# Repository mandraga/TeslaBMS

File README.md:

## Adaptation to Teensy 4.

This fork branches to adapt to the Teensy 4, it needs an interface board pcb or a carrier board redesign.
See the VW BMS fork or the pull request at the original repo for adapter PCB in Kicad format.

# TeslaBMS

Based off work done by Collin Kidder

Designed to work with my own board design and a Teensy 3.2

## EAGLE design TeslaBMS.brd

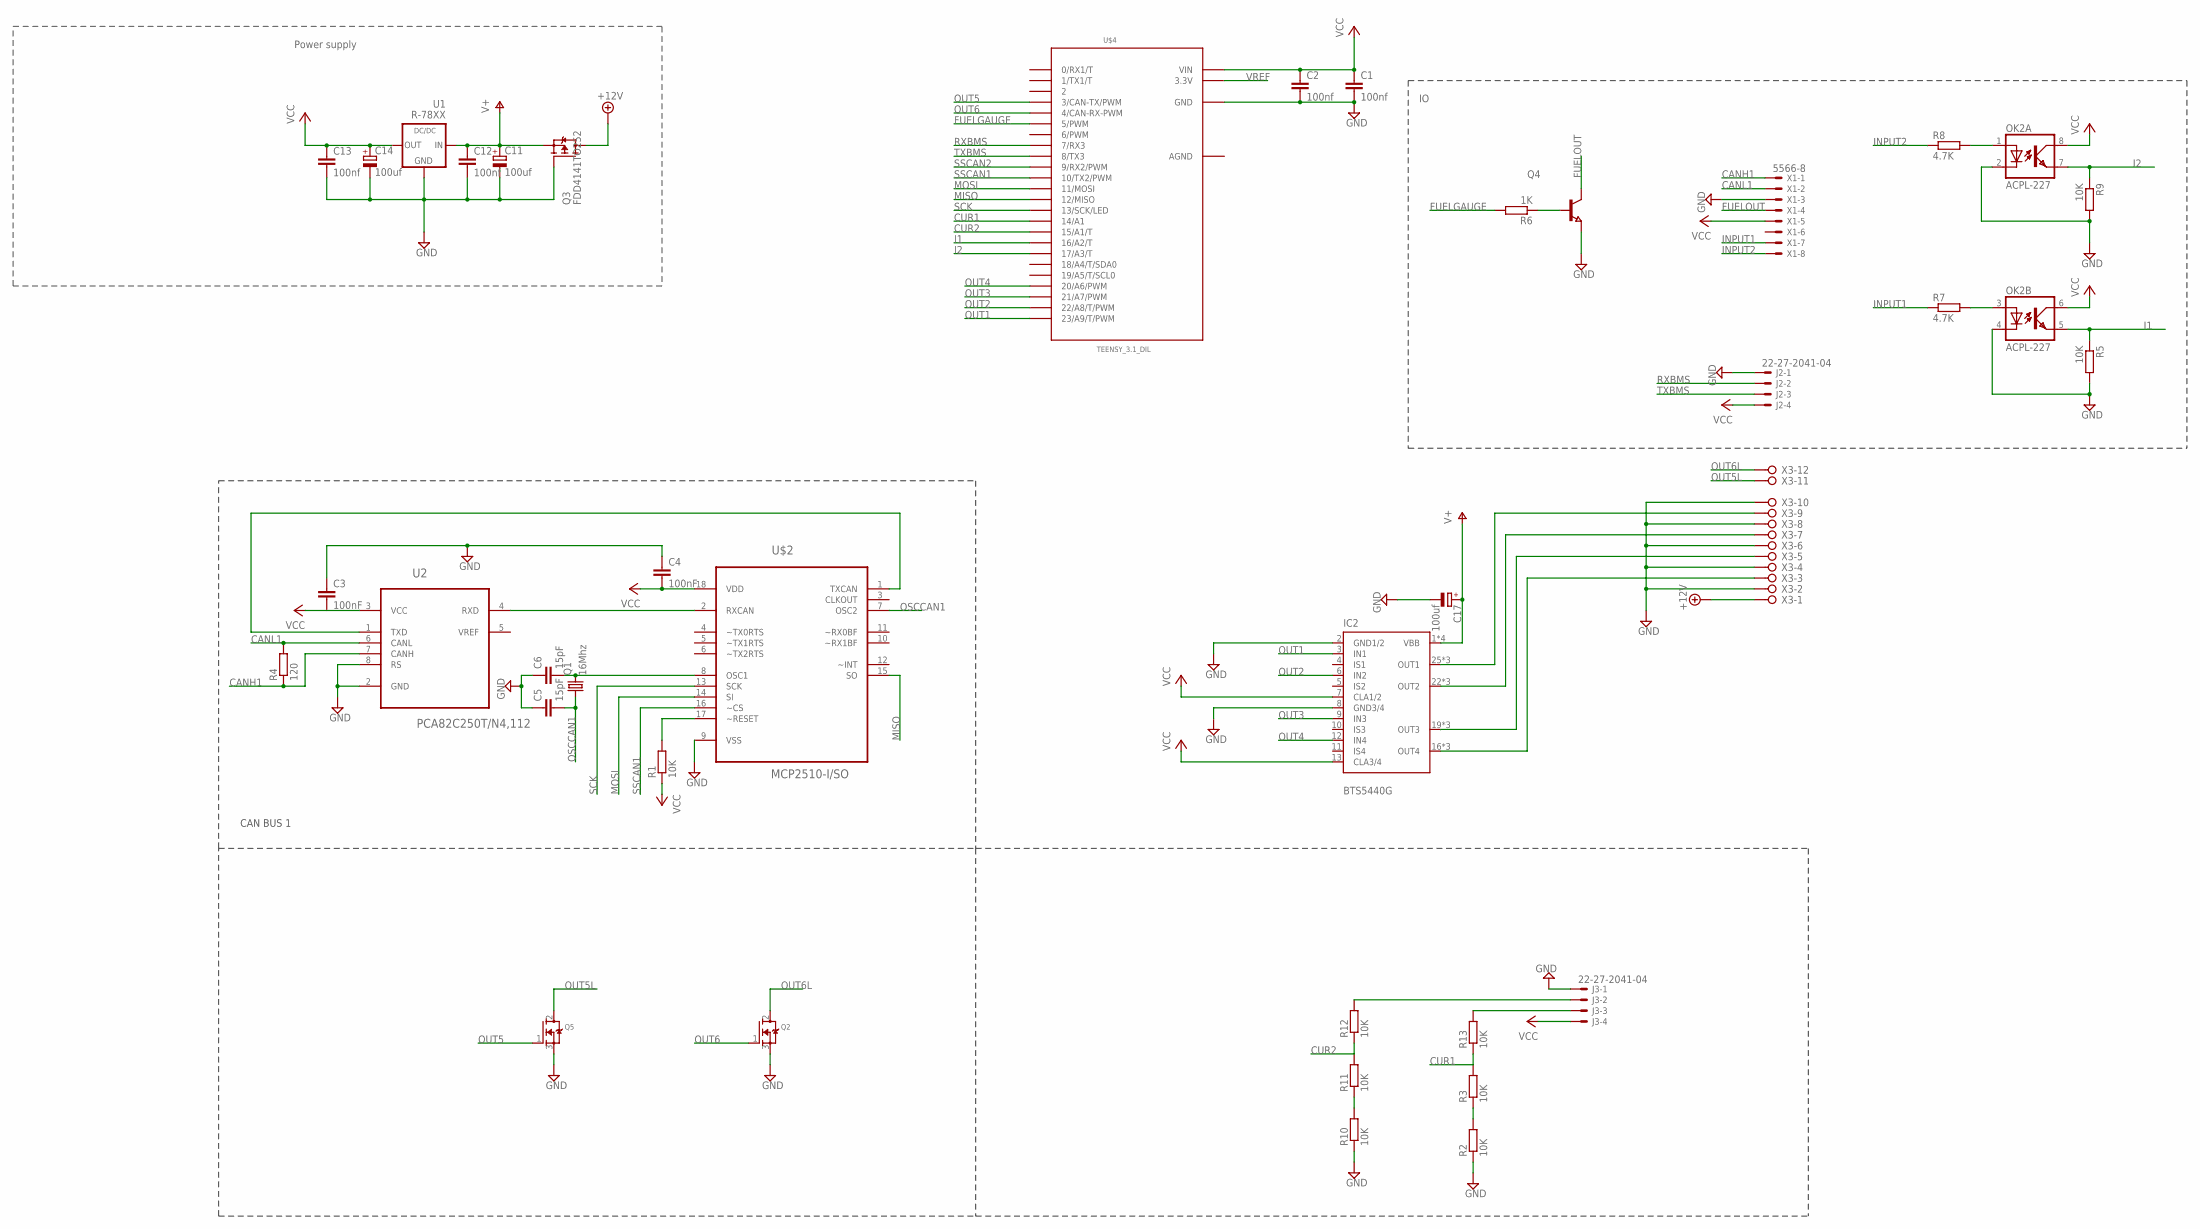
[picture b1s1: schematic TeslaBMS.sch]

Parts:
C1, C2, C12, C13: 100nf; C0805
C3, C4: 100nF; C0805
C5, C6: 15pF; C0805
C11, C14, C17: 100uf; 153CLV-0810
IC2: BTS5440G; PG-DSO-28
J2, J3: 22-27-2041-04; 6410-04
OK2: ACPL-227; SOIC08
Q1: 16Mhz; SM49
Q2, Q5: MOSFET-NGDS_TO220V; TO220V
Q3: FDD4141TO252; TO252
Q4: NPN-TRANSISTOR_SOT23; SOT23
R1, R2, R3, R5, R9, R10, R11, R12, R13: 10K; R0805
R4: 120; R0805
R6: 1K; R0805
R7, R8: 4.7K; R0805
U1: R-78XX
U2: PCA82C250T/N4,112; SOIC127P600X175-8N
U$2: MCP2510-I/SO; SOIC127P1034X264-18N
U$4: TEENSY_3.1_DIL; TEENSY3-DIL
X1: 5566-8
X3: W237-12P

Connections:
+12V: Q3.3 (D), X3.1
AGND: U$4.AGND
CANH1: R4.1, U2.7 (CANH), X1.1
CANH2: J3.3, R13.2
CANL1: R4.2, U2.6 (CANL), X1.2
CANL2: J3.2, R12.2
CUR1: R3.2, R13.1, U$4.14/A0 (14/A1)
CUR2: R11.2, R12.1, U$4.15/A1 (15/A1/T)
FUELGAUGE: R6.2, U$4.5 (5/PWM)
FUELOUT: Q4.3 (C), X1.4
GND: C1.2, C2.2, C3.1, C4.1, C5.1, C6.1, C11.-, C12.2, C13.2, C14.-, C17.-, IC2.2 (GND1/2), IC2.8 (GND3/4), J2.1, J3.1, OK2.2 (C), OK2.4 (C), Q2.3 (S), Q3.1 (G), Q4.2 (E), Q5.3 (S), R2.1, R5.2, R9.2, R10.1, U1.2 (GND), U2.2 (GND), U2.8 (RS), U$2.9 (VSS), U$4.GND, X1.3, X3.2, X3.4, X3.6, X3.8, X3.10
I1: OK2.5 (EMIT), R5.1, U$4.16/A2 (16/A2/T)
I2: OK2.7 (EMIT), R9.1, U$4.17/A3 (17/A3/T)
INPUT1: R7.1, X1.7
INPUT2: R8.1, X1.8
MISO: U$2.15 (SO), U$4.12 (12/MISO)
MOSI: U$2.14 (SI), U$4.11 (11/MOSI)
unnamed: U2.4 (RXD), U$2.2 (RXCAN)
unnamed: U2.1 (TXD), U$2.1 (TXCAN)
unnamed: R1.2, U$2.17 (~RESET)
unnamed: R2.2, R3.1
unnamed: R10.2, R11.1
unnamed: C6.2, Q1.2, U$2.8 (OSC1)
unnamed: Q4.1 (B), R6.1
unnamed: OK2.3 (A), R7.2
unnamed: OK2.1 (A), R8.2
unnamed: IC2.22 (OUT2), IC2.23 (OUT2), IC2.24 (OUT2), X3.7
unnamed: IC2.19 (OUT3), IC2.20 (OUT3), IC2.21 (OUT3), X3.5
unnamed: IC2.16 (OUT4), IC2.17 (OUT4), IC2.18 (OUT4), X3.3
unnamed: IC2.25 (OUT1), IC2.26 (OUT1), IC2.27 (OUT1), X3.9
OSCCAN1: C5.2, Q1.1, U$2.7 (OSC2)
OUT1: IC2.3 (IN1), U$4.23/A9 (23/A9/T/PWM)
OUT2: IC2.6 (IN2), U$4.22/A8 (22/A8/T/PWM)
OUT3: IC2.9 (IN3), U$4.21/A7 (21/A7/PWM)
OUT4: IC2.12 (IN4), U$4.20/A6 (20/A6/PWM)
OUT5: Q5.1 (G), U$4.3 (3/CAN-TX/PWM)
OUT5L: Q5.2 (D), X3.11
OUT6: Q2.1 (G), U$4.4 (4/CAN-RX-PWM)
OUT6L: Q2.2 (D), X3.12
RXBMS: J2.2, U$4.7 (7/RX3)
SCK: U$2.13 (SCK), U$4.13 (13/SCK/LED)
SSCAN1: U$2.16 (~CS), U$4.10 (10/TX2/PWM)
SSCAN2: U$4.9 (9/RX2/PWM)
TXBMS: J2.3, U$4.8 (8/TX3)
V+: C11.+, C12.1, C17.+, IC2.1 (VBB), IC2.14 (VBB), IC2.15 (VBB), IC2.28 (VBB), Q3.2 (S), U1.1 (IN)
VCC: C1.1, C2.1, C3.2, C4.2, C13.1, C14.+, IC2.7 (CLA1/2), IC2.13 (CLA3/4), J2.4, J3.4, OK2.6 (COL), OK2.8 (COL), R1.1, U1.3 (OUT), U2.3 (VCC), U$2.18 (VDD), U$4.VIN, X1.5
VREF: U$4.3.3V

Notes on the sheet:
Power supply
CAN BUS 1

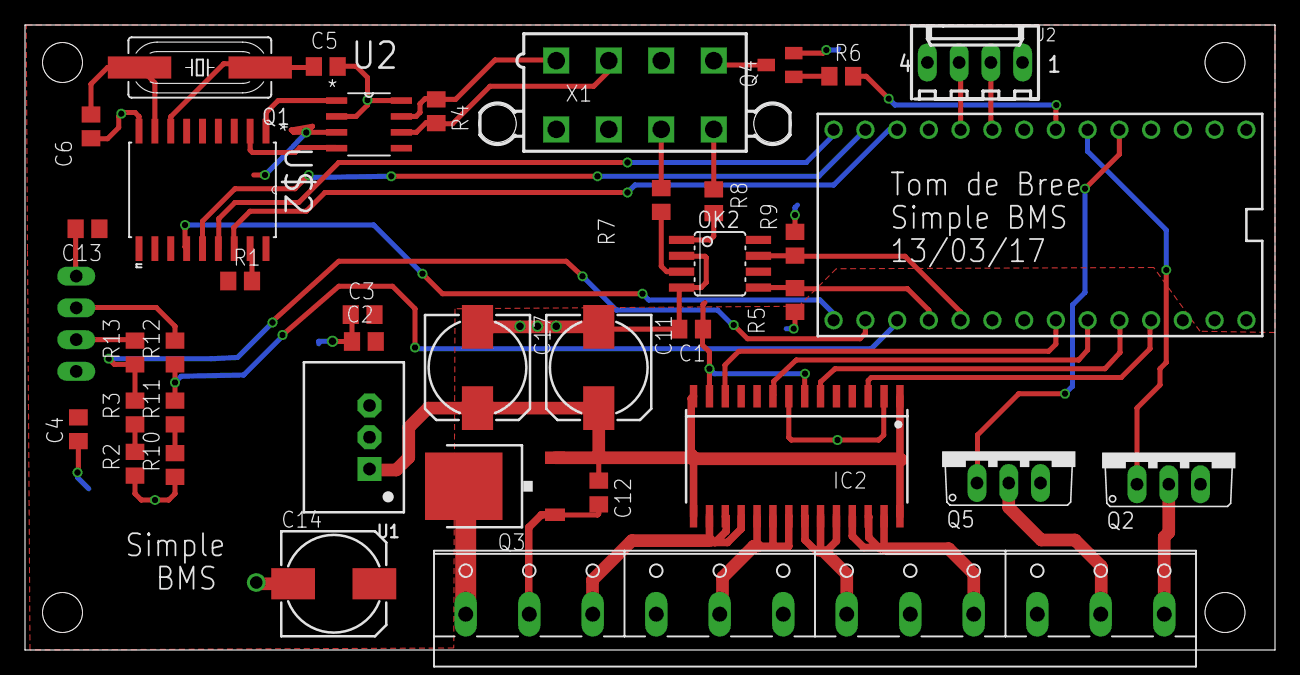
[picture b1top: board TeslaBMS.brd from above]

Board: 2 copper layers, 100.0 x 50.0 mm, 39 parts (1 on the bottom side), 44 nets.

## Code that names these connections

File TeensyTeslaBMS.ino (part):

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const int ACUR2 = A1; // current 2
const int IN1 = 16; // input 1 - high active
const int IN2 = 17; // input 2- high active
const int OUT1 = 20;// output 1 - high active
const int OUT2 = 21;// output 1 - high active
const int OUT3 = 23;// output 1 - high active
const int OUT4 = 24;// output 1 - high active
const int OUT5 = 3;// output 1 - high active
const int OUT6 = 4;// output 1 - high active
const int FUEL = 5;// Fuel gauge pwm signal
const int led = 13;

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  pinMode(ACUR2, INPUT);
  pinMode(IN1, INPUT);
  pinMode(IN2, INPUT);
  pinMode(OUT1, OUTPUT); // drive contactor
  pinMode(OUT2, OUTPUT); // precharge
  pinMode(OUT3, OUTPUT); // charge relay
  pinMode(OUT4, OUTPUT); // Negative contactor
  pinMode(OUT5, OUTPUT); // pwm driver output
  pinMode(OUT6, OUTPUT); // pwm driver output
  pinMode(FUEL, OUTPUT);
  pinMode(led, OUTPUT);

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
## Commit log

2017-02-19 Update TeslaBMS.ino
    need to use the right starting register when comparing in the response
2017-02-19 Update and rename TeslaBMS.ino to TeslaBMSteensy.ino
    Code now specific for Teensy 3.1, implemented changes needed from Collin's version.
2017-02-19 Update TeslaBMSteensy.ino
    Changes to organize the recognition of the adreses and assigning the 00 devices
2017-02-19 Update TeslaBMSteensy.ino
    Cleaned up the start up cylce.
    1. look for addresses on bus that are none 00
    2. Run a look for 00 addresses, these then get set against none used address identified in 1
    3. Enter loop and read out all values for the active slave modules (identified or assigned bus addresses)
2017-02-19 Update TeslaBMSteensy.ino
    Added a debug function to hide the uart traffic pass through
    Created line headers for converted data on serial output
2018-01-03 Update 03/01/18
    Update: SOC calc and some contactor control tweaks.
    Next: Canbus communication with Victron modules. Plus refinement of SOC calc
2018-01-21 SOC calc implementation and Canbus implementation
    Added can bus implementation, this allows broadcasting of voltage and current as well as battery limits.
    SOC calc has been improved, start point now defined by a voltage curve.
2018-01-23 No longer used
2018-01-24 Added bms method getHighCellVolt, modified the bmsstatus case statement to use this for balancing. fixed a few other bugs.
2018-02-16 Refining Current Sensor Usage
    Added:
    - start to implementing Can Based Current Sensor.
    - disconnected current sensor does not cause any SOC or Amphour change
    Removed:
    -None
2018-02-16 Wiped Jarrods Changes
    Fixed
2018-02-16 CAB300 Support
    No capable of working with the CAB300 on adress 0x3C2.
    To Toggle between analogue input or CAB300 go into Setup and then toggle sensor type.
2018-02-17 Moved UV check out of state machine
    All UV faults now result in error, moved out of statemachine to force BMS data to be read first.
2018-02-18 SOC reset at high end tweaking
2018-03-20 Added parallel strings and Ignore none connected cells
    Added parallel strings to correct voltage
    Ignore none connected cells via simple compare, voltage below 0.1V does not count for average.
2018-03-23 fixed charge/discharge limits and added menu for them
    fixed charge/discharge limits and added menu for them.
    Max setable currents are 3200A
2018-03-25 Created Alarm output structure and current scaling to temperature
    Now implemented alarm structure for Victron.
    Now allowed charge /discharge current is temperature dependant.
    Also corrected ignoring unconnected cell channels.
2018-03-25 More features for MB Tesla Boards
    Now added the abilty to ignore temp sensors
    Also improved ignoring unconnected cells
2018-03-26 Update with Settings for Voltage Ignoring
    Unconnected cells can cause voltage annoyance, this will create unwanted errors.
    Also turned on candebug for the current sensor.
2018-03-27 Output Control Fixes
    Turns out i miss numbered the outputs. Also fixed ensuring a turn-off with a loss of signal during precharge.
2018-04-01 Refresh canbus every few hours
    Canbus reintialize to combat controller locking up.
2018-04-05 new can library
    new can library
2018-04-13 update
    can problems trouble shooting
2018-12-09 Added CSV Output
2025-08-08 Renames CONFIG.H to config.h, adds a .gitignore file.
2025-08-08 Applies the modifications as in the VWBMS fork.
    The #include <mcp2515.h> still causes a compilaiton error. Must be
    investigated. The Teensy 4.0 has more cans so maybe it could do without
    it or we can delete this form the code if the CAN is not used.
2025-08-12 Fixing the compilation, read DOCUMENTATION.md
2025-08-12 Explains the fork purpose.
